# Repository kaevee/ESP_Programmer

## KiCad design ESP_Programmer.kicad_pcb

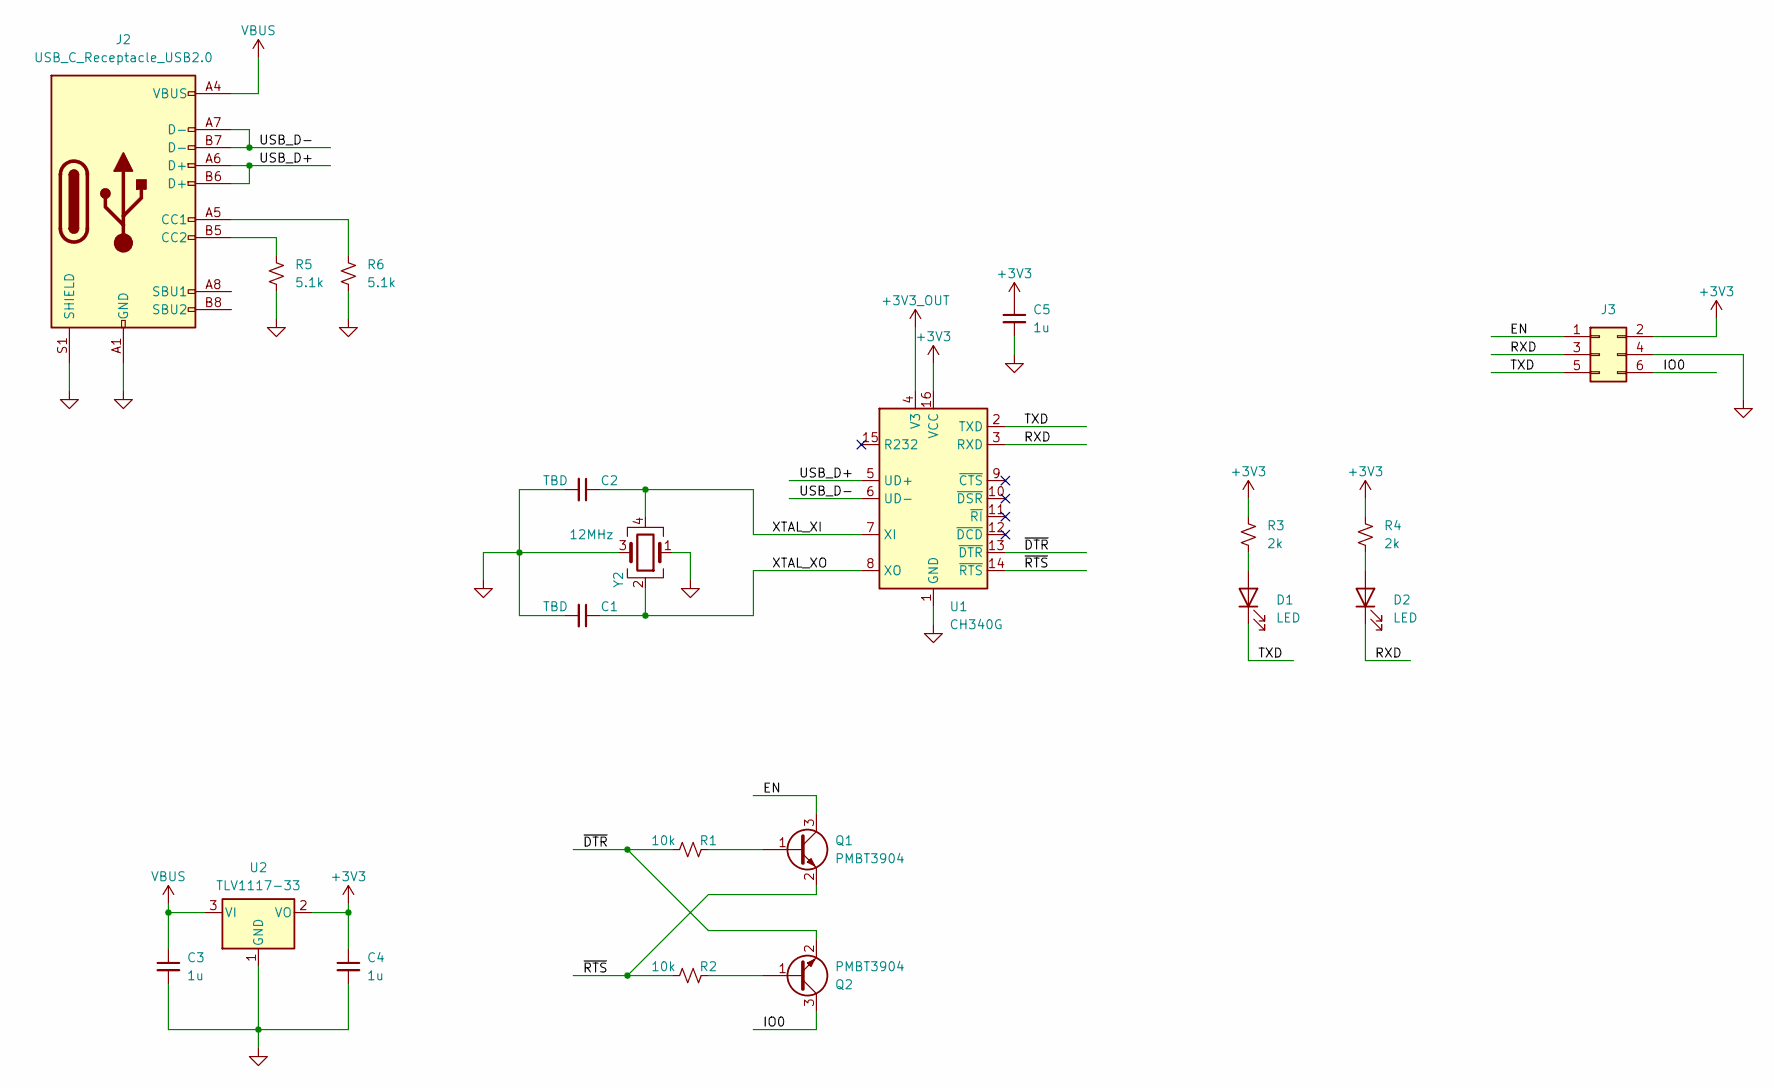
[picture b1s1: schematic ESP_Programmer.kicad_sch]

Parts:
C1, C2: TBD; C_0805_2012Metric_Pad1.18x1.45mm_HandSolder
C3, C4: 1u; C_0805_2012Metric
C5: 1u; C_0805_2012Metric_Pad1.18x1.45mm_HandSolder
D1, D2: LED; LED_0805_2012Metric_Pad1.15x1.40mm_HandSolder
J2: USB_C_Receptacle_USB2.0; USB_C_Receptacle_HRO_TYPE-C-31-M-12
J3: Conn_02x03_Odd_Even; PinHeader_2x03_P1.27mm_Vertical
Q1, Q2: PMBT3904; SOT-23
R1, R2: 10k; R_0805_2012Metric_Pad1.20x1.40mm_HandSolder
R3, R4: 2k; R_0805_2012Metric_Pad1.20x1.40mm_HandSolder
R5, R6: 5.1k; R_0805_2012Metric_Pad1.20x1.40mm_HandSolder
U1: CH340G; SOIC-16_3.9x9.9mm_P1.27mm
U2: TLV1117-33; SOT-223-3_TabPin2
Y2: 12MHz; Crystal_SMD_3225-4Pin_3.2x2.5mm

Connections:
+3V3: C4.1, C5.1, J3.2, R3.1, R4.1, U1.16 (VCC), U2.2 (VO)
+3V3_OUT: U1.4 (V3)
/EN: J3.1, Q1.3 (C)
/IO0: J3.6, Q2.3 (C)
/RXD: D2.1 (K), J3.3, U1.3 (RXD)
/TXD: D1.1 (K), J3.5, U1.2 (TXD)
/USB_D+: J2.A6 (D+), J2.B6 (D+), U1.5 (UD+)
/USB_D-: J2.A7 (D-), J2.B7 (D-), U1.6 (UD-)
/XTAL_XI: C2.1, U1.7 (XI), Y2.4
/XTAL_XO: C1.1, U1.8 (XO), Y2.2
/~DTR: Q2.2 (E), R1.1, U1.13 (~DTR)
/~RTS: Q1.2 (E), R2.1, U1.14 (~RTS)
GND: C1.2, C2.2, C3.2, C4.2, C5.2, J2.A1 (GND), J2.A12 (GND), J2.B1 (GND), J2.B12 (GND), J2.S1 (SHIELD), J3.4, R5.2, R6.2, U1.1 (GND), U2.1 (GND), Y2.1, Y2.3
unnamed: D1.2 (A), R3.2
unnamed: D2.2 (A), R4.2
unnamed: J2.A5 (CC1), R6.1
unnamed: J2.B5 (CC2), R5.1
unnamed: Q1.1 (B), R1.2
unnamed: Q2.1 (B), R2.2
VBUS: C3.1, J2.A4 (VBUS), J2.A9 (VBUS), J2.B4 (VBUS), J2.B9 (VBUS), U2.3 (VI)

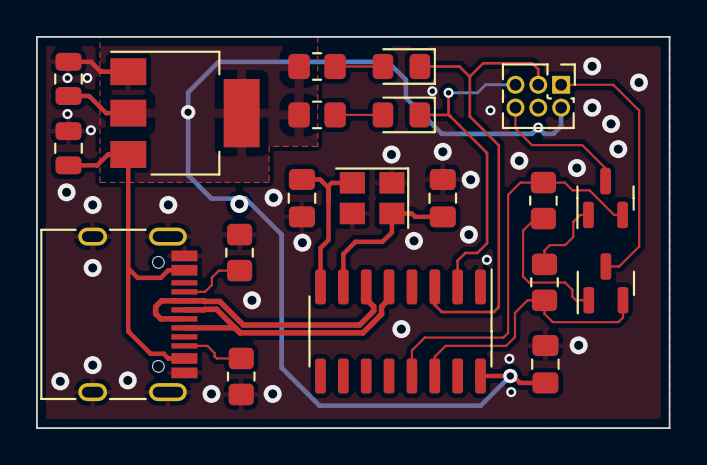
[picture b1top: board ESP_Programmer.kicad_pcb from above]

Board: 4 copper layers, 35.2 x 21.7 mm, 20 parts (0 on the bottom side), 19 nets.

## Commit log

2023-10-02 Added 3D view
2023-10-02 Fixed typo in image URL
